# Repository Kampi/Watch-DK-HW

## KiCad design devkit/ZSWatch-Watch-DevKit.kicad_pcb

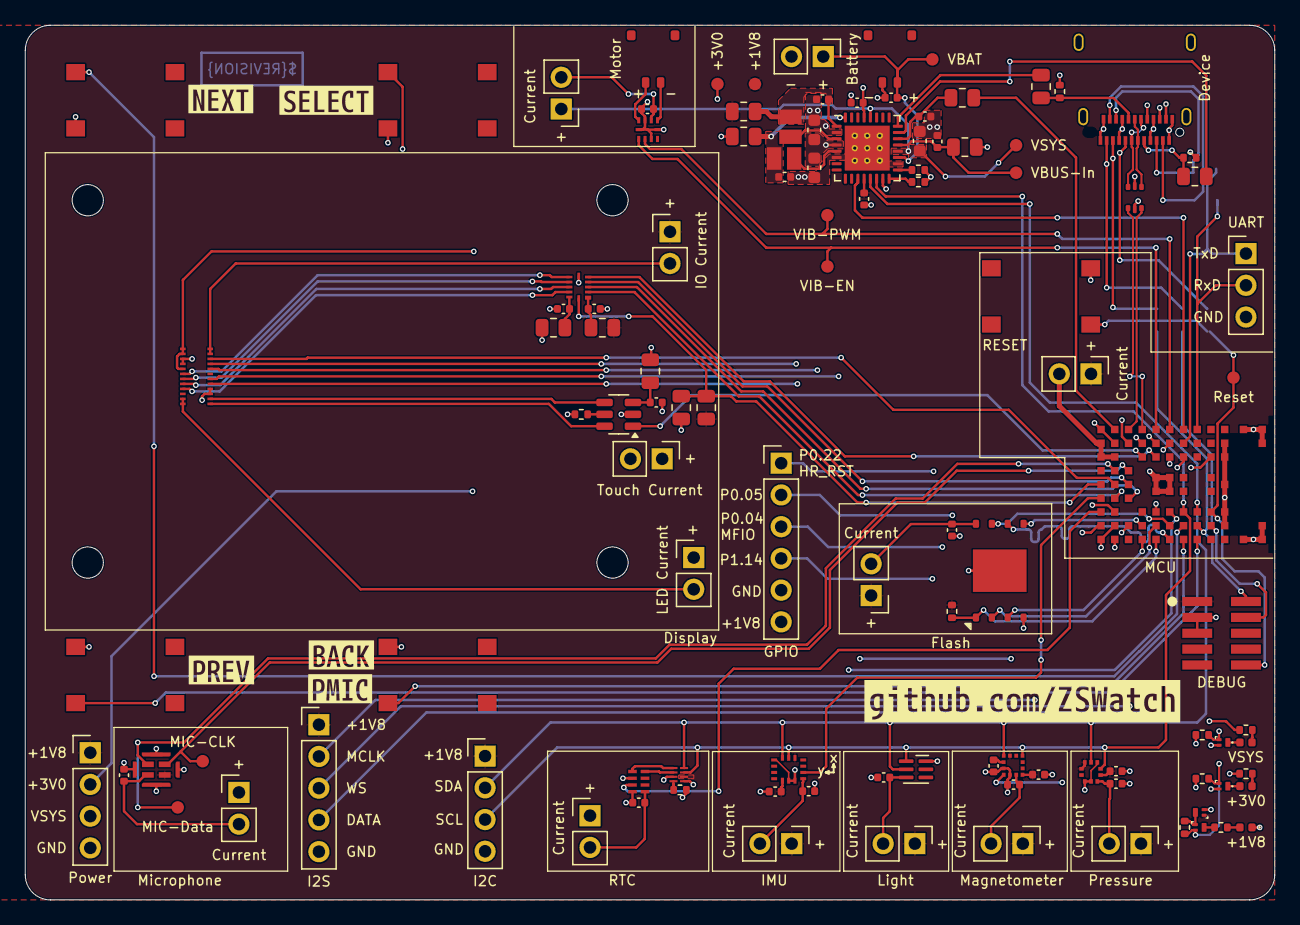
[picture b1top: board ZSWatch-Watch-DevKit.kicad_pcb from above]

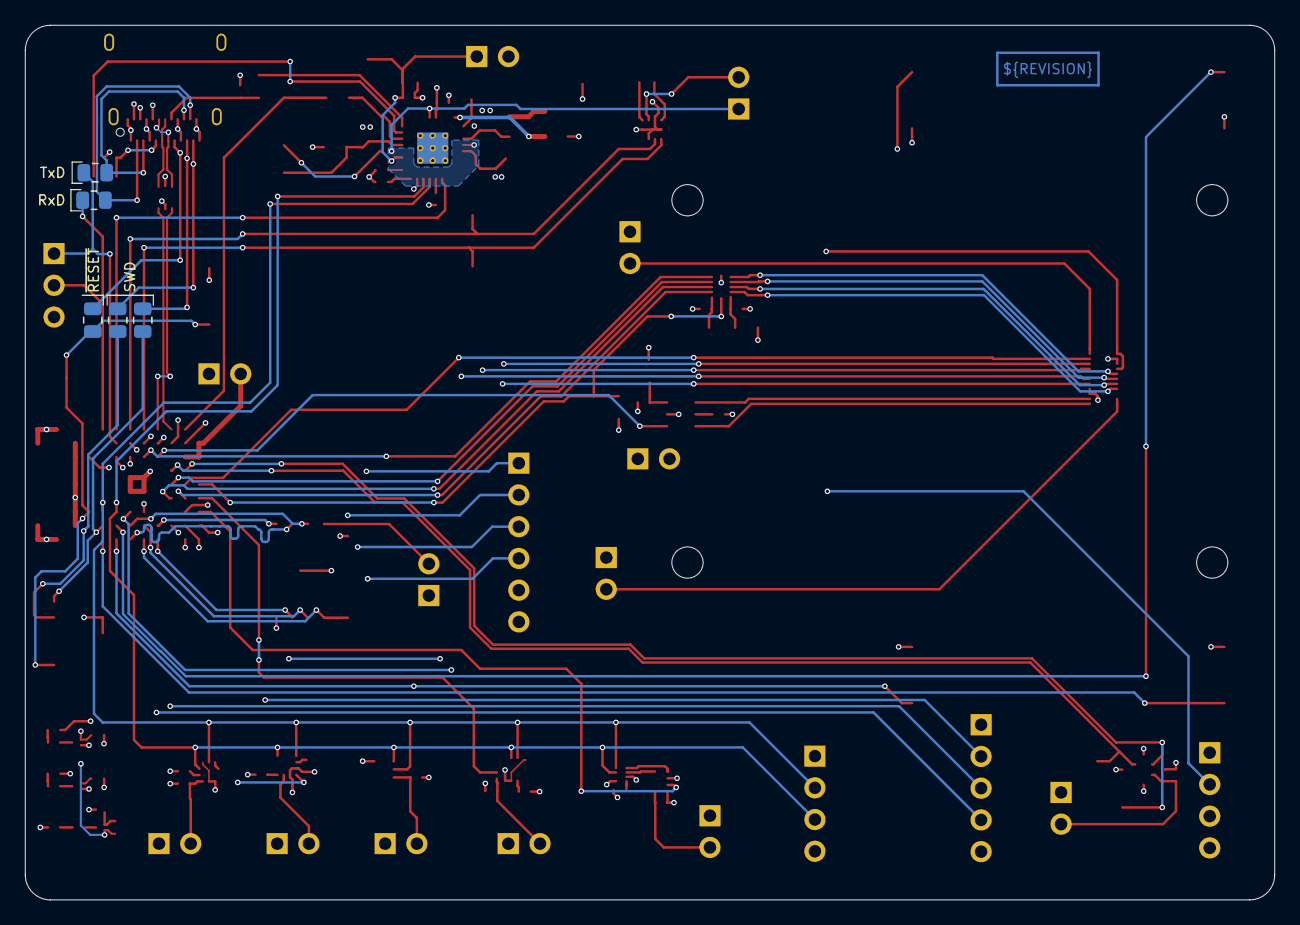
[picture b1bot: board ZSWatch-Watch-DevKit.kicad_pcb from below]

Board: 4 copper layers, 100.0 x 70.0 mm, 121 parts (5 on the bottom side), 107 nets.

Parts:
C401, C404, C601: 1u; C_0402_1005Metric
C402, C501, C502, C503, C504, C507, C508, C509, C510, C511, C602, C603, C604: 100n; C_0402_1005Metric
C403: 2u2; C_0402_1005Metric
C405, C407, C410, C506: 10u; C_0402_1005Metric
C406, C408, C409: 10u; C_0603_1608Metric
C505: 220n; C_0402_1005Metric
D401: +3V0; LED_0402_1005Metric
D402: VSYS; LED_0402_1005Metric
D403: +1V8; LED_0402_1005Metric
IC401: nPM1300-QEXX; QFN-32-1EP_5x5mm_P0.5mm_EP3.6x3.6mm_ThermalVias
IC501: APDS-9306-065; Broadcom_DFN-6_2x2mm_P0.65mm
IC502: BMI270; Bosch_LGA-14_3x2.5mm_P0.5mm_LayoutBorder3x4y
IC503: LIS2MDLTR; LGA-12_2x2mm_P0.5mm
IC504: BMP581; Bosch_LGA-10_2x2mm_P0.5mm_ClockwisePinNumbering
IC505: DRV2603RUNT; WQFN-10_2x2mm_P0.5mm
IC506: PCA9306JK; XSON-8_0.65x0.17mm_P0.35mm
IC507: RV-8263-C8
IC601: FAN5622SX; TSOT-23-6
IC602: USBLC6-2P6; SOT-666
IC603: MX25U51245GZ4I00; WSON-8-1EP_8x6mm_P1.27mm_EP3.4x4.3mm
IC604: NTS0104GU12; XQFN-12-1.7x2mm_P0.4mm
L401, L402: 2u2; L_0806_2016
M601: NORA-B106
MK501: SPK0641HT4H-1
Q401, Q402, Q403: PMZ550UNEYL; DFN-1006-3
Q404: PMZB320UPEYL; DFN-1006-3
R401, R402, R403, R408, R502, R612: 100k; R_0402_1005Metric
R404, R405, R406: 560R; R_0402_1005Metric
R407: 47k; R_0402_1005Metric
R409, R410, R411, R412, R602, R605, R606, R607, R608, R609, R610, R611, R615, R616: 0R; R_0805_2012Metric
R601: 12k; R_0402_1005Metric
R603, R604: 5k1; R_0402_1005Metric
R613, R614: 100k; R_0805_2012Metric
S501: SW1; WS-TASV-6x6
S502: SW2; WS-TASV-6x6
S503: SW3; WS-TASV-6x6
S504: SW4; WS-TASV-6x6
S601: RESET; WS-TASV-6x6
TP401: VBUS-In; TestPoint_Pad_D1.0mm
TP402: VBAT; TestPoint_Pad_D1.0mm
TP403: +1V8; TestPoint_Pad_D1.0mm
TP404: +3V0; TestPoint_Pad_D1.0mm
TP405: VSYS; TestPoint_Pad_D1.0mm
TP501: VIB-EN; TestPoint_Pad_D1.0mm
TP502: VIB-PWM; TestPoint_Pad_D1.0mm
TP503: MIC-CLK; TestPoint_Pad_D1.0mm
TP504: MIC-Data; TestPoint_Pad_D1.0mm
TP601: Reset; TestPoint_Pad_D1.0mm
X401: Battery; PinHeader_1x02_P2.54mm_Vertical
X402: Battery; 78171-0002
X403: Power; PinHeader_1x04_P2.54mm_Vertical
X501, X503, X505, X506, X507, X508, X510, X602, X606: Current; PinHeader_1x02_P2.54mm_Vertical
X502: I2S; PinHeader_1x05_P2.54mm_Vertical
X504: I2C; PinHeader_1x04_P2.54mm_Vertical
X509: Motor; 78171-0002
X601: DEBUG; SHF-105-01-L-D-SM-TR
X603: Device; USB_C_Receptacle_Amphenol_12401610E4-2A
X604: UART; PinHeader_1x03_P2.54mm_Vertical
X605: GPIO; PinHeader_1x06_P2.54mm_Vertical
X607: IO Current; PinHeader_1x02_P2.54mm_Vertical
X608: Display; ER-CON0.4-24P
X609: Touch Current; PinHeader_1x02_P2.54mm_Vertical
X610: LED Current; PinHeader_1x02_P2.54mm_Vertical
kibuzzard-683075F5: G***; kibuzzard-683075F5
kibuzzard-6830428E: G***; kibuzzard-6830428E
kibuzzard-68303879: G***; kibuzzard-68303879
kibuzzard-68304278: G***; kibuzzard-68304278
kibuzzard-68304289: G***; kibuzzard-68304289
kibuzzard-68304292: G***; kibuzzard-68304292

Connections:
+1V8: C402.1, C503.1, C506.1, C508.2, IC401.12 (V_{IO}), IC502.5 (VDDIO), IC502.12 (CSB), IC503.3 (CS), IC503.10 (VDDIO), IC504.1 (VDDIO), IC504.5 (SDO), IC504.6 (CSB), IC506.2 (VCC_{1}), MK501.3 (SEL), Q401.G, R410.1, R612.1, R613.2, R615.2, TP403.1, X403.1, X501.1, X502.1, X504.1, X505.1, X506.1, X507.1, X601.1 (VTref), X602.1, X605.6, X606.1, X607.1
+3V0: R404.2, R411.1, R602.1, R616.2, TP404.1, X403.2, X609.1, X610.1
/Project Architecture/MCU/BMI270-INT: IC502.9 (INT2), M601.A4 (P1.00)
/Project Architecture/MCU/D+: IC602.1 (I/O1), X603.A6 (D+), X603.B6 (D+)
/Project Architecture/MCU/D-: IC602.3 (I/O2), X603.A7 (D-), X603.B7 (D-)
/Project Architecture/MCU/Data: M601.J7 (P1.10), X502.4
/Project Architecture/MCU/LIS2MDL-INT: IC503.7 (INT/DRDY), M601.E3 (P0.21)
/Project Architecture/MCU/MCLK: M601.F7 (P1.07), X502.2
/Project Architecture/MCU/MIC-CLK: M601.C6 (P0.00/XL1), MK501.2 (CLK), TP503.1
/Project Architecture/MCU/MIC-DATA: M601.B6 (P0.01/XL2), MK501.1 (DATA), TP504.1
/Project Architecture/MCU/PMIC-INT: IC401.11 (GPIO4), M601.G9 (P1.13)
/Project Architecture/MCU/SCL: IC401.14 (SCL), IC501.1 (SCL), IC502.13 (SCK), IC503.1 (SCL/SPC), IC504.2 (SCK), IC506.3 (SCL_{1}), M601.G3 (P0.25/AIN4), X504.3
/Project Architecture/MCU/SDA: IC401.13 (SDA), IC501.2 (SDA), IC502.14 (SDI), IC503.4 (SDA/SDI/SDO), IC504.4 (SDI), IC506.4 (SDA_{1}), M601.H3 (P0.27/AIN6), X504.2
/Project Architecture/MCU/SW1: M601.F3 (P0.19), S501.1
/Project Architecture/MCU/SW2: IC401.15 (SHPHLD), M601.G1 (P1.06), S502.2
/Project Architecture/MCU/SW3: M601.H1 (P0.24), S503.2
/Project Architecture/MCU/SW4: M601.G2 (P0.26/AIN5), S504.1
/Project Architecture/MCU/USB-CC1: IC401.23 (CC1), R605.2
/Project Architecture/MCU/USB-CC2: IC401.24 (CC2), R606.1
/Project Architecture/MCU/USB-VBUS-In: IC602.5 (VBUS), Q402.G, Q403.G, Q404.S, R401.1, R402.1, R403.1, R409.1, X603.A4 (VBUS), X603.A9 (VBUS), X603.B4 (VBUS), X603.B9 (VBUS)
/Project Architecture/MCU/USB-VBUS-Out: M601.B9 (VBUS), R412.2
/Project Architecture/MCU/VIB-EN: IC505.1 (EN), M601.E9 (P1.05), TP501.1
/Project Architecture/MCU/VIB-PWM: IC505.2 (PWM), M601.F9 (P1.15), TP502.1
/Project Architecture/MCU/WS: M601.G7 (P1.09), X502.3
/Project Architecture/MCU/~RTC-INT: IC507.3 (~INT), M601.A3 (P1.03/I2C)
/Project Architecture/Peripherals/VBAT: C403.1, IC401.19 (V_{BAT}), IC506.7 (VCC_{2}), R502.2, TP402.1, X401.1, X402.1, X510.1
/Project Architecture/Peripherals/VMIC: C410.1, IC401.29 (LSOUT1/VOUTLDO1), X503.1
/Project Architecture/Power Management/VBUS-In: C401.1, IC401.21 (V_{BUS}), R409.2, TP401.1
/Project Architecture/Power Management/VSYS: C406.1, C408.1, C409.1, IC401.4 (V_{DD}), IC401.20 (V_{SYS}), IC401.28 (LSIN1/VINLDO1), R405.2, TP405.1, X403.3, X508.1
DISPLAY-BLK: IC601.1 (CTRL), M601.D7 (P0.23)
DISPLAY-CLK: M601.B1 (P0.08/TRACEDATA[3]), X608.8 (SCL)
DISPLAY-CS: M601.B3 (P0.11/TRACEDATA[0]), X608.9 (CS)
DISPLAY-DATA: M601.C2 (P0.09/TRACEDATA[2]), X608.6 (SDI/SDA)
DISPLAY-DC: M601.A2 (P0.12/TRACECLK), X608.5 (RS/DC)
DISPLAY-EN: IC604.12 (OE), M601.A5 (P0.20), R613.1, R614.2
DISPLAY-RST: M601.B5 (P0.03/NFC2), X608.10 (RESET)
GND: C401.2, C402.2, C403.2, C404.2, C405.2, C406.2, C407.2, C408.2, C409.2, C410.2, C501.2, C502.2, C503.2, C504.1, C505.2, C506.2, C507.2, C508.1, C509.2, C510.2, C511.2, C601.1, C602.1, C603.2, C604.2, D403.1 (K), IC401.2 (PVSS1), IC401.6 (PVSS2), IC401.18 (NTC), IC401.33 (GND), IC501.6 (GND), IC502.1 (SDO), IC502.6 (GND), IC502.7 (GND), IC503.6 (GND), IC503.8 (GND), IC504.3 (GND), IC504.8 (GND), IC504.9 (GND), IC505.3 (LRA/~ERM), IC505.5 (GND), IC505.8 (GND), IC505.10 (GND), IC506.1 (GND), IC507.2 (CLKOE), IC507.4 (GND), IC601.2 (GND), IC602.2 (GND), IC603.4 (GND), IC603.9 (EP), IC604.6 (GND), M601.A1 (GND), M601.A9 (GND), M601.B2 (GND), M601.B8 (GND), M601.E4 (GND), M601.E5 (GND), M601.F4 (GND), M601.F5 (GND), M601.K2 (GND), M601.K3 (GND), M601.K5 (GND), M601.K7 (GND), M601.K8 (GND), M601.L1 (GND), M601.L9 (GND), M601.M1 (GND), M601.M2 (GND), M601.M8 (GND), M601.M9 (GND), MK501.5 (GND), MK501.6 (GND), MK501.7 (GND), MK501.8 (GND), Q401.S, Q402.S, Q403.S, R401.2, R402.2, R407.1, R408.1, R601.1, R603.2, R604.1, R614.1, S501.2, S502.1, S503.1, S504.2, S601.2, X401.2, X402.2, X403.4, X502.5, X504.4, X601.3 (GND), X601.5 (GND), X603.A1 (GND), X603.A12 (GND), X603.B1 (GND), X603.B12 (GND), X603.S1 (SHIELD), X604.3, X605.5, X608.3 (GND), X608.4 (GND), X608.15 (GND), X608.16 (GND)
LEDK1: IC601.6 (LED1), X608.1 (LEDK-1)
LEDK2: IC601.4 (LED2), X608.2 (LEDK-2)
unnamed: D401.2 (A), R404.1
unnamed: D401.1 (K), Q402.D
unnamed: D402.2 (A), R405.1
unnamed: D402.1 (K), Q403.D
unnamed: D403.2 (A), R406.1
unnamed: IC401.3 (SW1), L402.2
unnamed: IC401.5 (SW2), L401.2
unnamed: C404.1, IC401.22 (VBUS_{OUT}), R412.1
unnamed: C407.1, IC401.1 (VOUT1), L402.1, R410.2
unnamed: C405.1, IC401.32 (VOUT2), L401.1, R411.2
unnamed: IC401.17 (VSET1), R407.2
unnamed: IC401.16 (VSET2), R408.2
unnamed: C501.1, IC501.3 (VDD), X501.2
unnamed: C504.2, IC502.8 (VDD), X505.2
unnamed: C505.1, IC503.5 (C1)
unnamed: C507.1, IC503.9 (VDD), X506.2
unnamed: C509.1, IC504.10 (VDD), X507.2
unnamed: IC505.9 (OUT+), X509.2
unnamed: IC505.6 (OUT-), X509.1
unnamed: C510.1, IC505.7 (VDD), X508.2
unnamed: IC506.8 (EN), R502.1
unnamed: IC506.6 (SCL_{2}), IC507.8 (SCL)
unnamed: IC506.5 (SDA_{2}), IC507.1 (SDA)
unnamed: C511.1, IC507.5 (V_{DD}), X510.2
unnamed: IC601.5 (ISET), R601.2
unnamed: C601.2, IC601.3 (VIN), R602.2
unnamed: C602.2, IC603.8 (VCC), X606.2
unnamed: IC604.10 (B1), X608.21 (CTP-INT)
unnamed: IC604.9 (B2), X608.20 (CTP-SCL)
unnamed: IC604.8 (B3), X608.19 (CTP-SDA)
unnamed: IC604.7 (B4), X608.18 (CTP-RST)
unnamed: C603.1, IC604.1 (VCCA), R615.1
unnamed: C604.1, IC604.11 (VCCB), R616.1
unnamed: M601.A7 (VDD), M601.A8 (VDDH), M601.B7 (VDD), X602.2
unnamed: M601.D8 (P0.04/AIN0), X605.3
unnamed: M601.E8 (P0.05/AIN1), X605.2
unnamed: M601.C8 (P0.22), X605.1
unnamed: M601.F8 (P1.14), X605.4
unnamed: C502.1, MK501.4 (VDD), X503.2
unnamed: Q401.D, Q404.G, R403.2
unnamed: Q404.D, R406.2
unnamed: R603.1, R605.1, X603.A5 (CC1)
unnamed: R604.2, R606.2, X603.B5 (CC2)
unnamed: R608.2, X603.A11 (RX2+), X603.B11 (RX1+)
unnamed: R607.2, X603.A10 (RX2-), X603.B10 (RX1-)
unnamed: R611.2, X603.A8 (SBU1), X603.B8 (SBU2)
unnamed: R609.2, X603.A2 (TX1+), X603.B2 (TX2+)
unnamed: R610.2, X603.A3 (TX1-), X603.B3 (TX2-)
unnamed: X607.2, X608.11 (VDDIO), X608.12 (VDDIO)
unnamed: X608.13 (VDD), X608.14 (VDD), X608.17 (CTP-VDD), X609.2
unnamed: X608.23 (LEDA2), X608.24 (LEDA1), X610.2
QSPI-CLK: IC603.6 (SCK), M601.F1 (P0.17/QSPI_CLK)
QSPI-CS: IC603.1 (~CS), M601.E1 (P0.18/QSPI_CS), R612.2
QSPI-IO0: IC603.5 (SI(I/O0)), M601.D2 (P0.13/QSPI[0])
QSPI-IO1: IC603.2 (SO(I/O1)), M601.E2 (P0.14/QSPI[1])
QSPI-IO2: IC603.3 (~WP(I/O2)), M601.D1 (P0.15/QSPI[2])
QSPI-IO3: IC603.7 (~HOLD(I/O3)), M601.F2 (P0.16/QSPI[3])
RESETn: M601.J3 (~RESET), R611.1, S601.1, TP601.1, X601.10 (~RESET)
RxD: M601.H9 (P1.11), R609.1, X604.2
SWDCLK: M601.J2 (SWDCLK), R608.1, X601.4 (SWCLK/TCK)
SWDIO: M601.H2 (SWDIO), R607.1, X601.2 (SWDIO/TMS)
TOUCH-INT: IC604.2 (A1), M601.B4 (P1.02/I2C)
TOUCH-RST: IC604.5 (A4), M601.E7 (P0.06/AIN2)
TOUCH-SCL: IC604.3 (A2), M601.C4 (P1.01)
TOUCH-SDA: IC604.4 (A3), M601.C5 (P0.02/NFC1)
TxD: M601.G8 (P1.12), R610.1, X604.1
USB-D+: IC602.6 (I/O1), M601.C9 (D+)
USB-D-: IC602.4 (I/O2), M601.D9 (D-)

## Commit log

2025-09-06 Release Watch-DK revision 1
    - Remove PCB prints from directory
2025-09-06 Prepare release
    - Remove old files
    - Update CI/CD pipeline
    - Fix ERC issues
    - Fix DRC issues
    - Update README
    - Add changelog for v1.2.0
2025-09-06 Update CHANGELOG
2025-09-06 Update outputs (release)
2025-09-07 Push outputs from CI/CD (2025-09-07 19:59:51)
